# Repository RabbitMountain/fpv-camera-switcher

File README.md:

# fpv-camera-switcher
FPV 3-way triple camera switcher board

Description

A small 3-way camera switcher board intended for hobby FPV or similar use. PWM input signal to switch between 3 cameras.

License

Rabbit Mountain Research invests time and resources providing this open source design, please support RMR and open-source hardware by purchasing products from Rabbit Mountain Research.

Designed by Andrew Barney for Rabbit Mountain Research. Still prototyping and working out bugs.

Hardware uses the CERN 2.0 OHL-S Licence. Software uses the GPL , all text above must be included in any redistribution. See license.txt for additional details.

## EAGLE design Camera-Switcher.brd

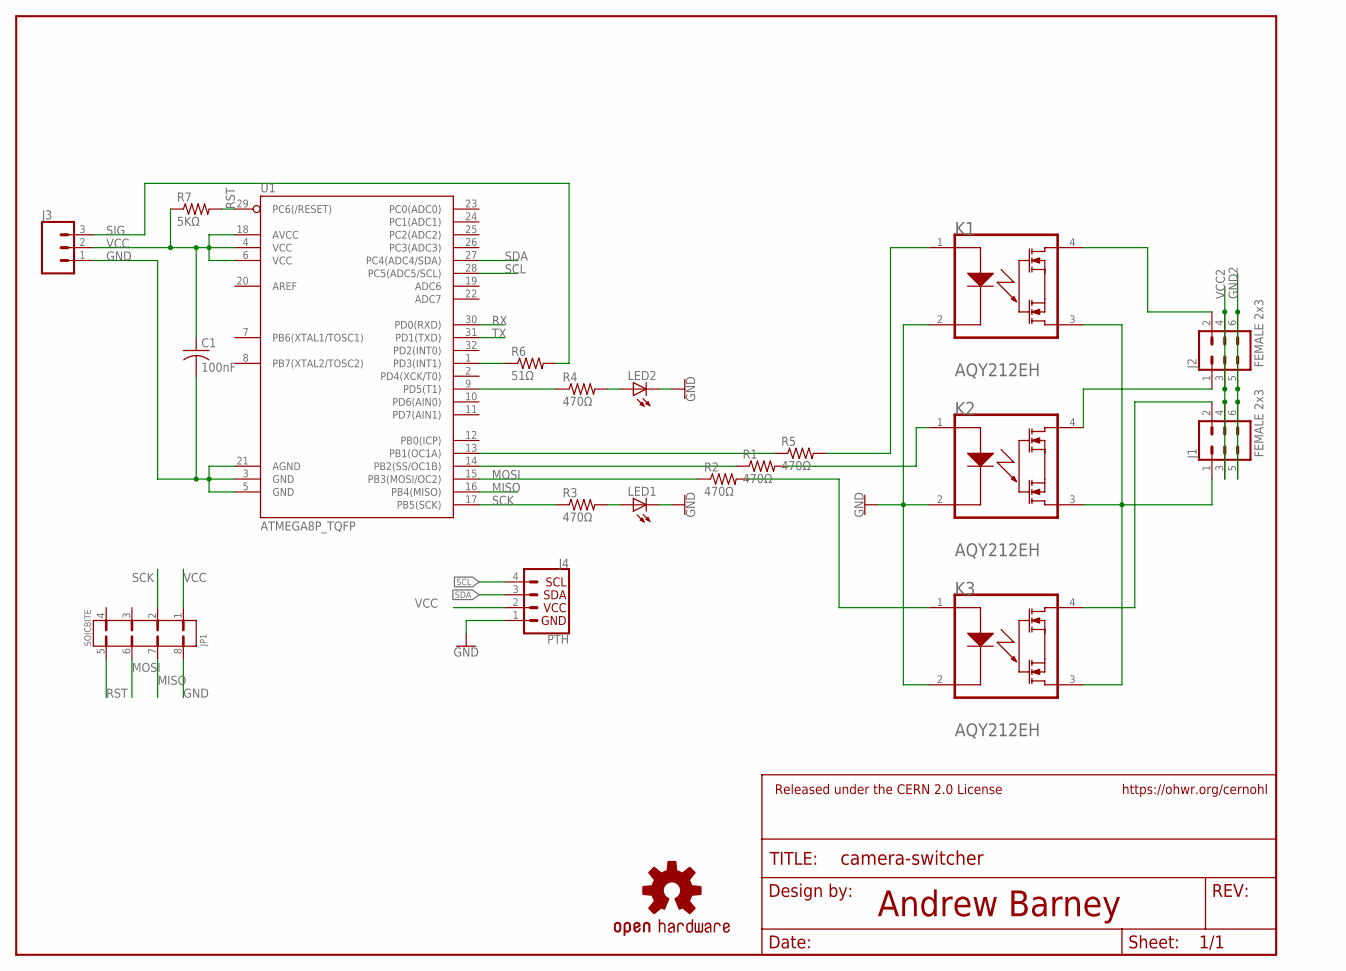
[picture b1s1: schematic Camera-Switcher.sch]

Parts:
C1: 100nF; C0805
FRAME1: FRAME-LETTER-CERN"; CERN-OHL-S
J1, J2: FEMALE 2x3; 2X3
J3: CONN_03; 1X03
J4: PTH; 1X04
JP1: SOICBITE; SOICBITE2
K1, K2, K3: PANASONIC_AQY212EHPANASONIC_AQY212EH_0_0; PANASONIC_AQY212EH_0
LED1, LED2: LEDCHIPLED_0805; CHIPLED_0805
LOGO1: OSHW-LOGOS; OSHW-LOGO-S
R1, R2, R3, R4, R5: 470Ω; R0805
R6: 51Ω; R0805
R7: 5KΩ; R0805
U1: ATMEGA8P_TQFP; TQFP32-08

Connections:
GND: C1.2, J3.1, J4.1, JP1.8, K1.2, K2.2, K3.2, LED1.C, LED2.C, U1.3 (GND), U1.5 (GND), U1.21 (AGND)
GND2: J1.5, J1.6, J2.5, J2.6
MISO: JP1.7, U1.16 (PB4(MISO))
MOSI: JP1.6, R2.1, U1.15 (PB3(MOSI/OC2))
unnamed: R6.1, U1.1 (PD3(INT1))
unnamed: LED1.A, R3.2
unnamed: LED2.A, R4.2
unnamed: R4.1, U1.9 (PD5(T1))
unnamed: R1.1, U1.14 (PB2(SS/OC1B))
unnamed: R5.1, U1.13 (PB1(OC1A))
unnamed: K3.1, R2.2
unnamed: K2.1, R1.2
unnamed: K1.1, R5.2
unnamed: J1.1, K1.3, K2.3, K3.3
unnamed: J1.2, K3.4
unnamed: J2.1, K2.4
unnamed: J2.2, K1.4
RST: JP1.5, R7.2, U1.29 (PC6(/RESET))
RX: U1.30 (PD0(RXD))
SCK: JP1.2, R3.1, U1.17 (PB5(SCK))
SCL: J4.4, U1.28 (PC5(ADC5/SCL))
SDA: J4.3, U1.27 (PC4(ADC4/SDA))
SIG: J3.3, R6.2
TX: U1.31 (PD1(TXD))
VCC: C1.1, J3.2, J4.2, JP1.1, R7.1, U1.4 (VCC), U1.6 (VCC), U1.18 (AVCC)
VCC2: J1.3, J1.4, J2.3, J2.4

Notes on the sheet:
Andrew Barney

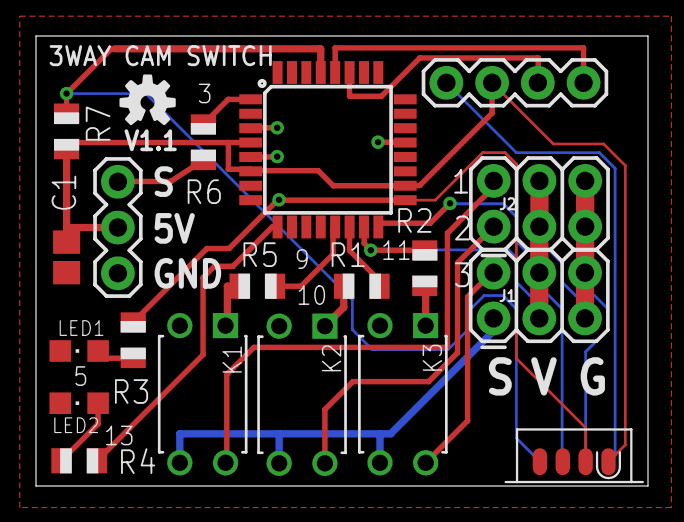
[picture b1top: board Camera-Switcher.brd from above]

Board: 2 copper layers, 34.0 x 25.0 mm, 22 parts (1 on the bottom side), 24 nets.

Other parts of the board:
U$1: RMR-SIT-10MM

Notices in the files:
parts and their libraries:
SparkFun-Connectors: Licensing: Creative Commons ShareAlike 4.0 International - https://creativecommons.org/licenses/by-sa/4.0
RMR: Hardware released under the CERN-OHL-S 2.0 License
RMR: Code is released under the GPL License
RMR: Hardware released under the CERN-OHL-P 2.0 License
